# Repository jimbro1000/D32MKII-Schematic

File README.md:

# Dragon 32 MKII Schematic

Captured in KiCad by Stewart Orchard 2015-2019

Original design by Dragon Data Ltd circa 1982

PCB Reproduction by Julian Brown 2023

## Why?

The published Dragon schematics do not appear to include MKII versions, which can be a problem for repairs as there are differences in the memory configuration, the video circuit and logic gate pin numbers. I captured this information around the year 1998 with reference to the existing ISS2 schematics, a multimeter and a real MKII ISS6 main board, and have finally got round to recording it as a KiCad project.

## Disclaimer

Much as I would like to think that I've got this 100% correct, there is always the chance that there are mistakes and omissions. I would recommend checking that the information is accurate before using this schematic for anything potentially expensive.

## PCB Design

The PCB layout has been added to further assist with rapid identification of components and 
interconnections between components

This is not an attempt to reverse-engineer the board for production and no support will be given

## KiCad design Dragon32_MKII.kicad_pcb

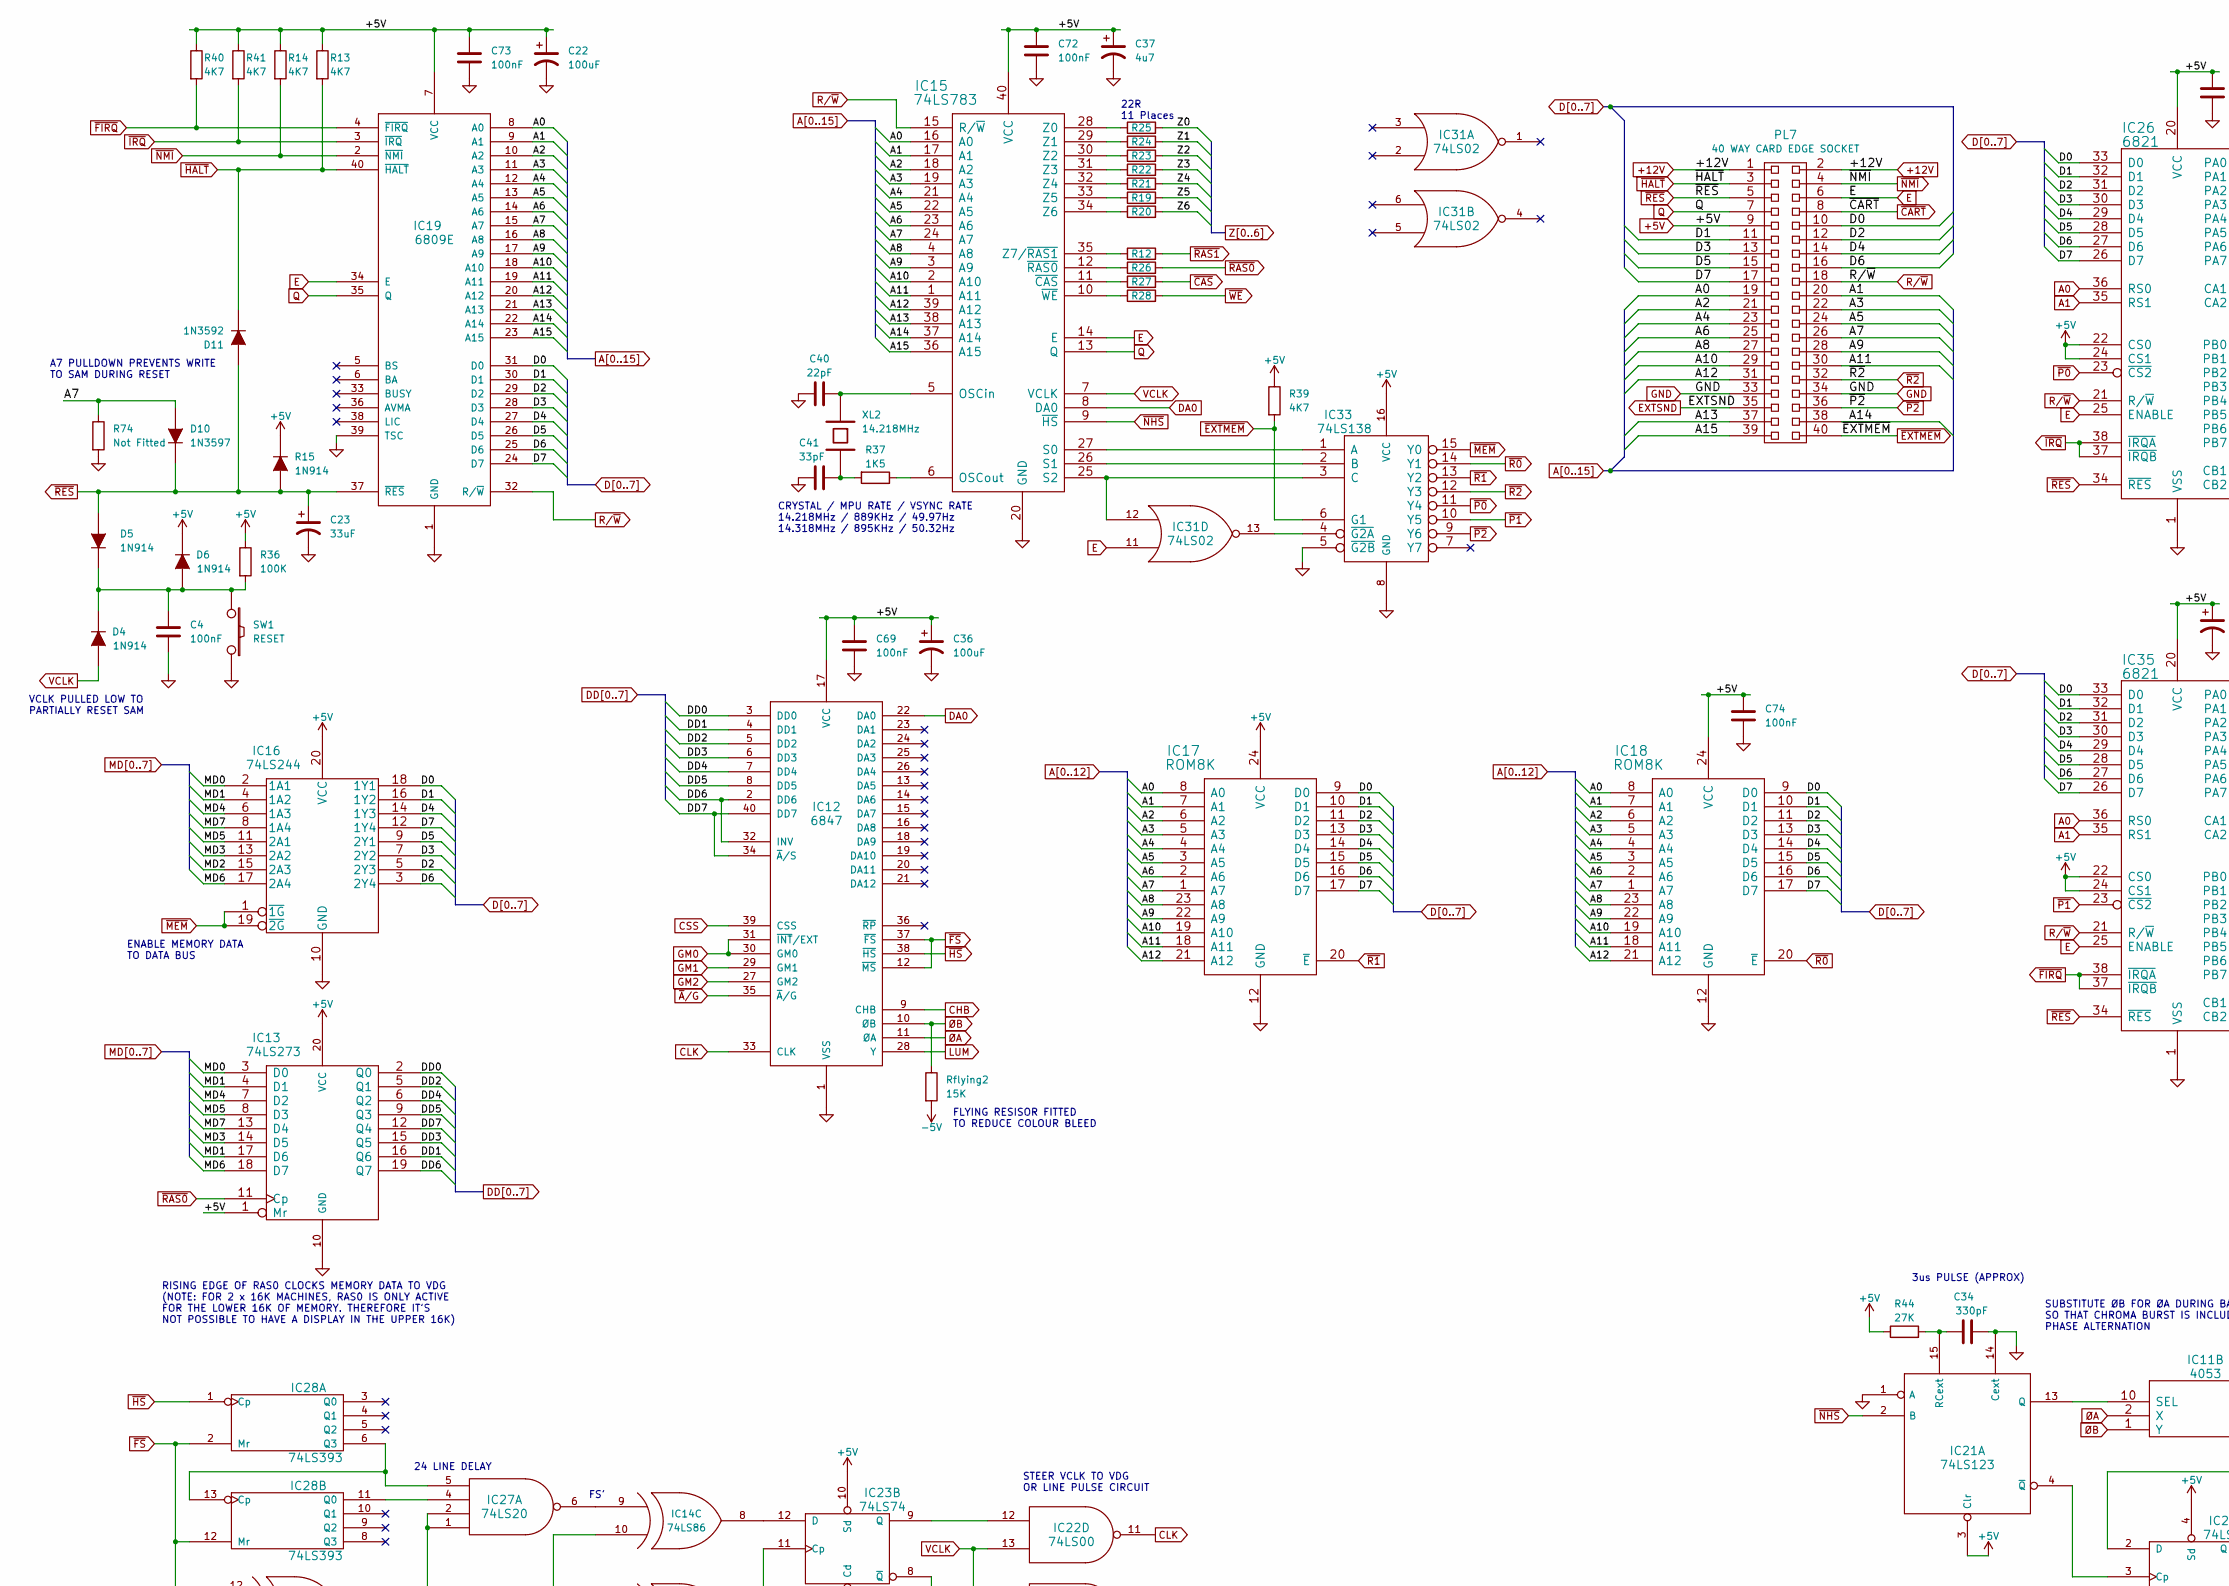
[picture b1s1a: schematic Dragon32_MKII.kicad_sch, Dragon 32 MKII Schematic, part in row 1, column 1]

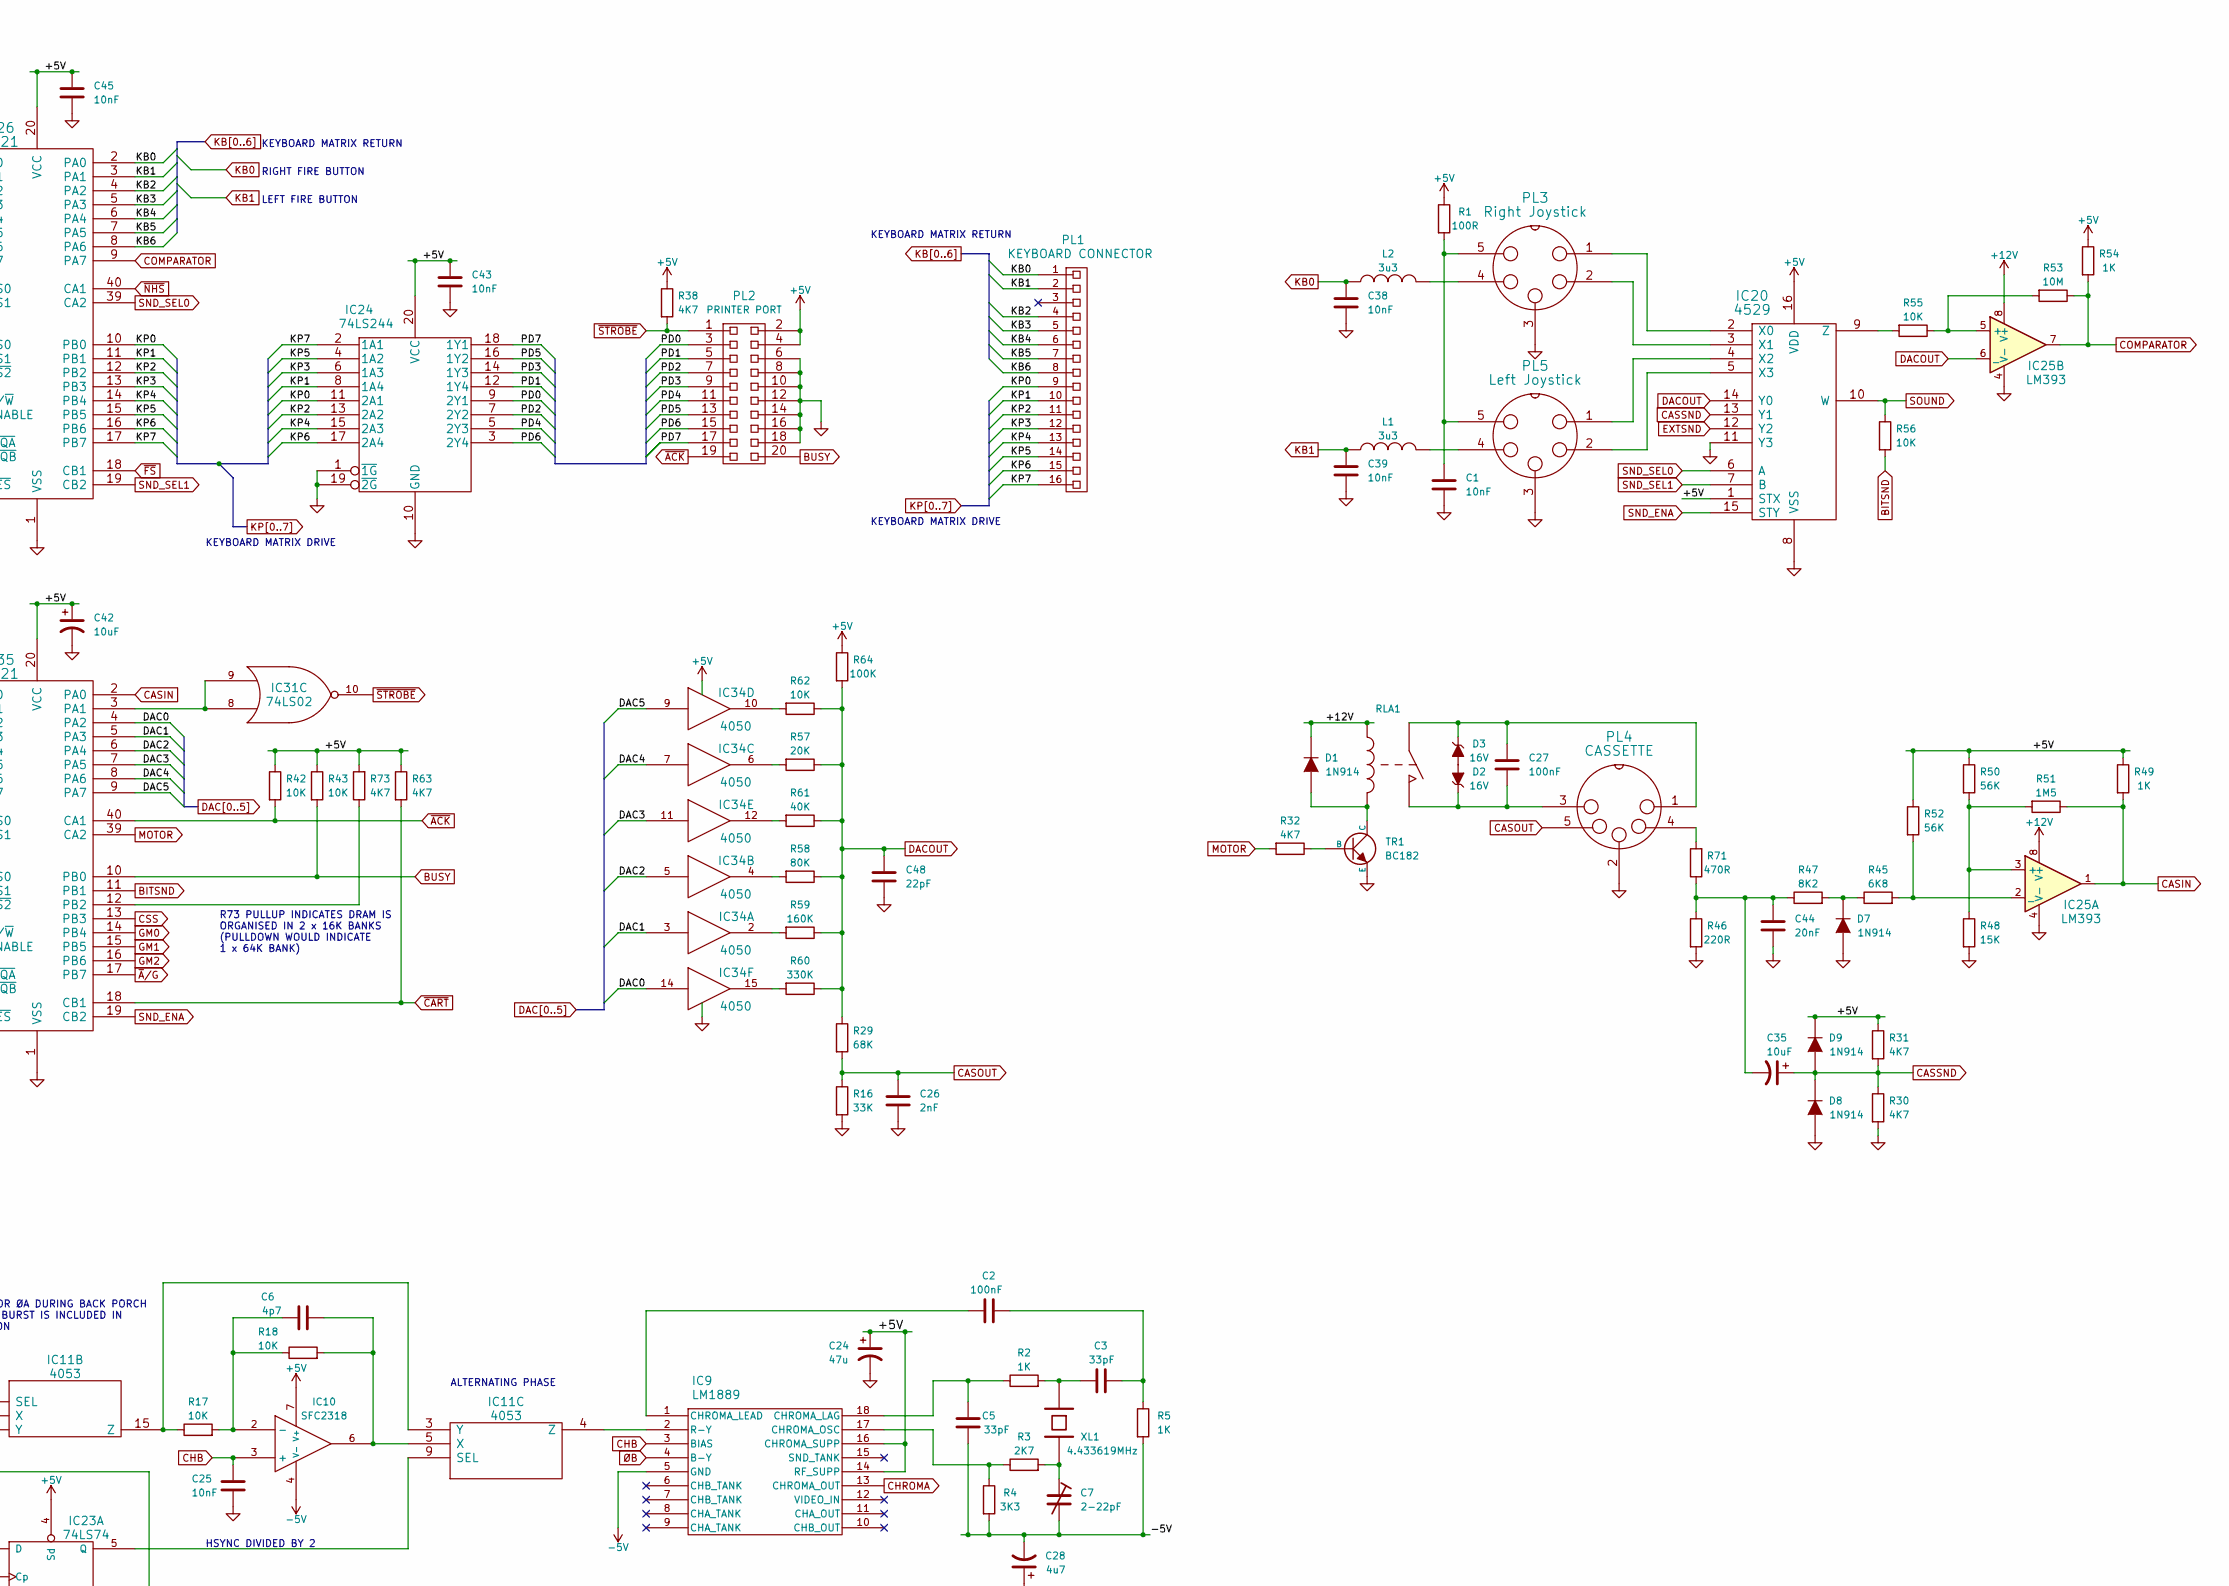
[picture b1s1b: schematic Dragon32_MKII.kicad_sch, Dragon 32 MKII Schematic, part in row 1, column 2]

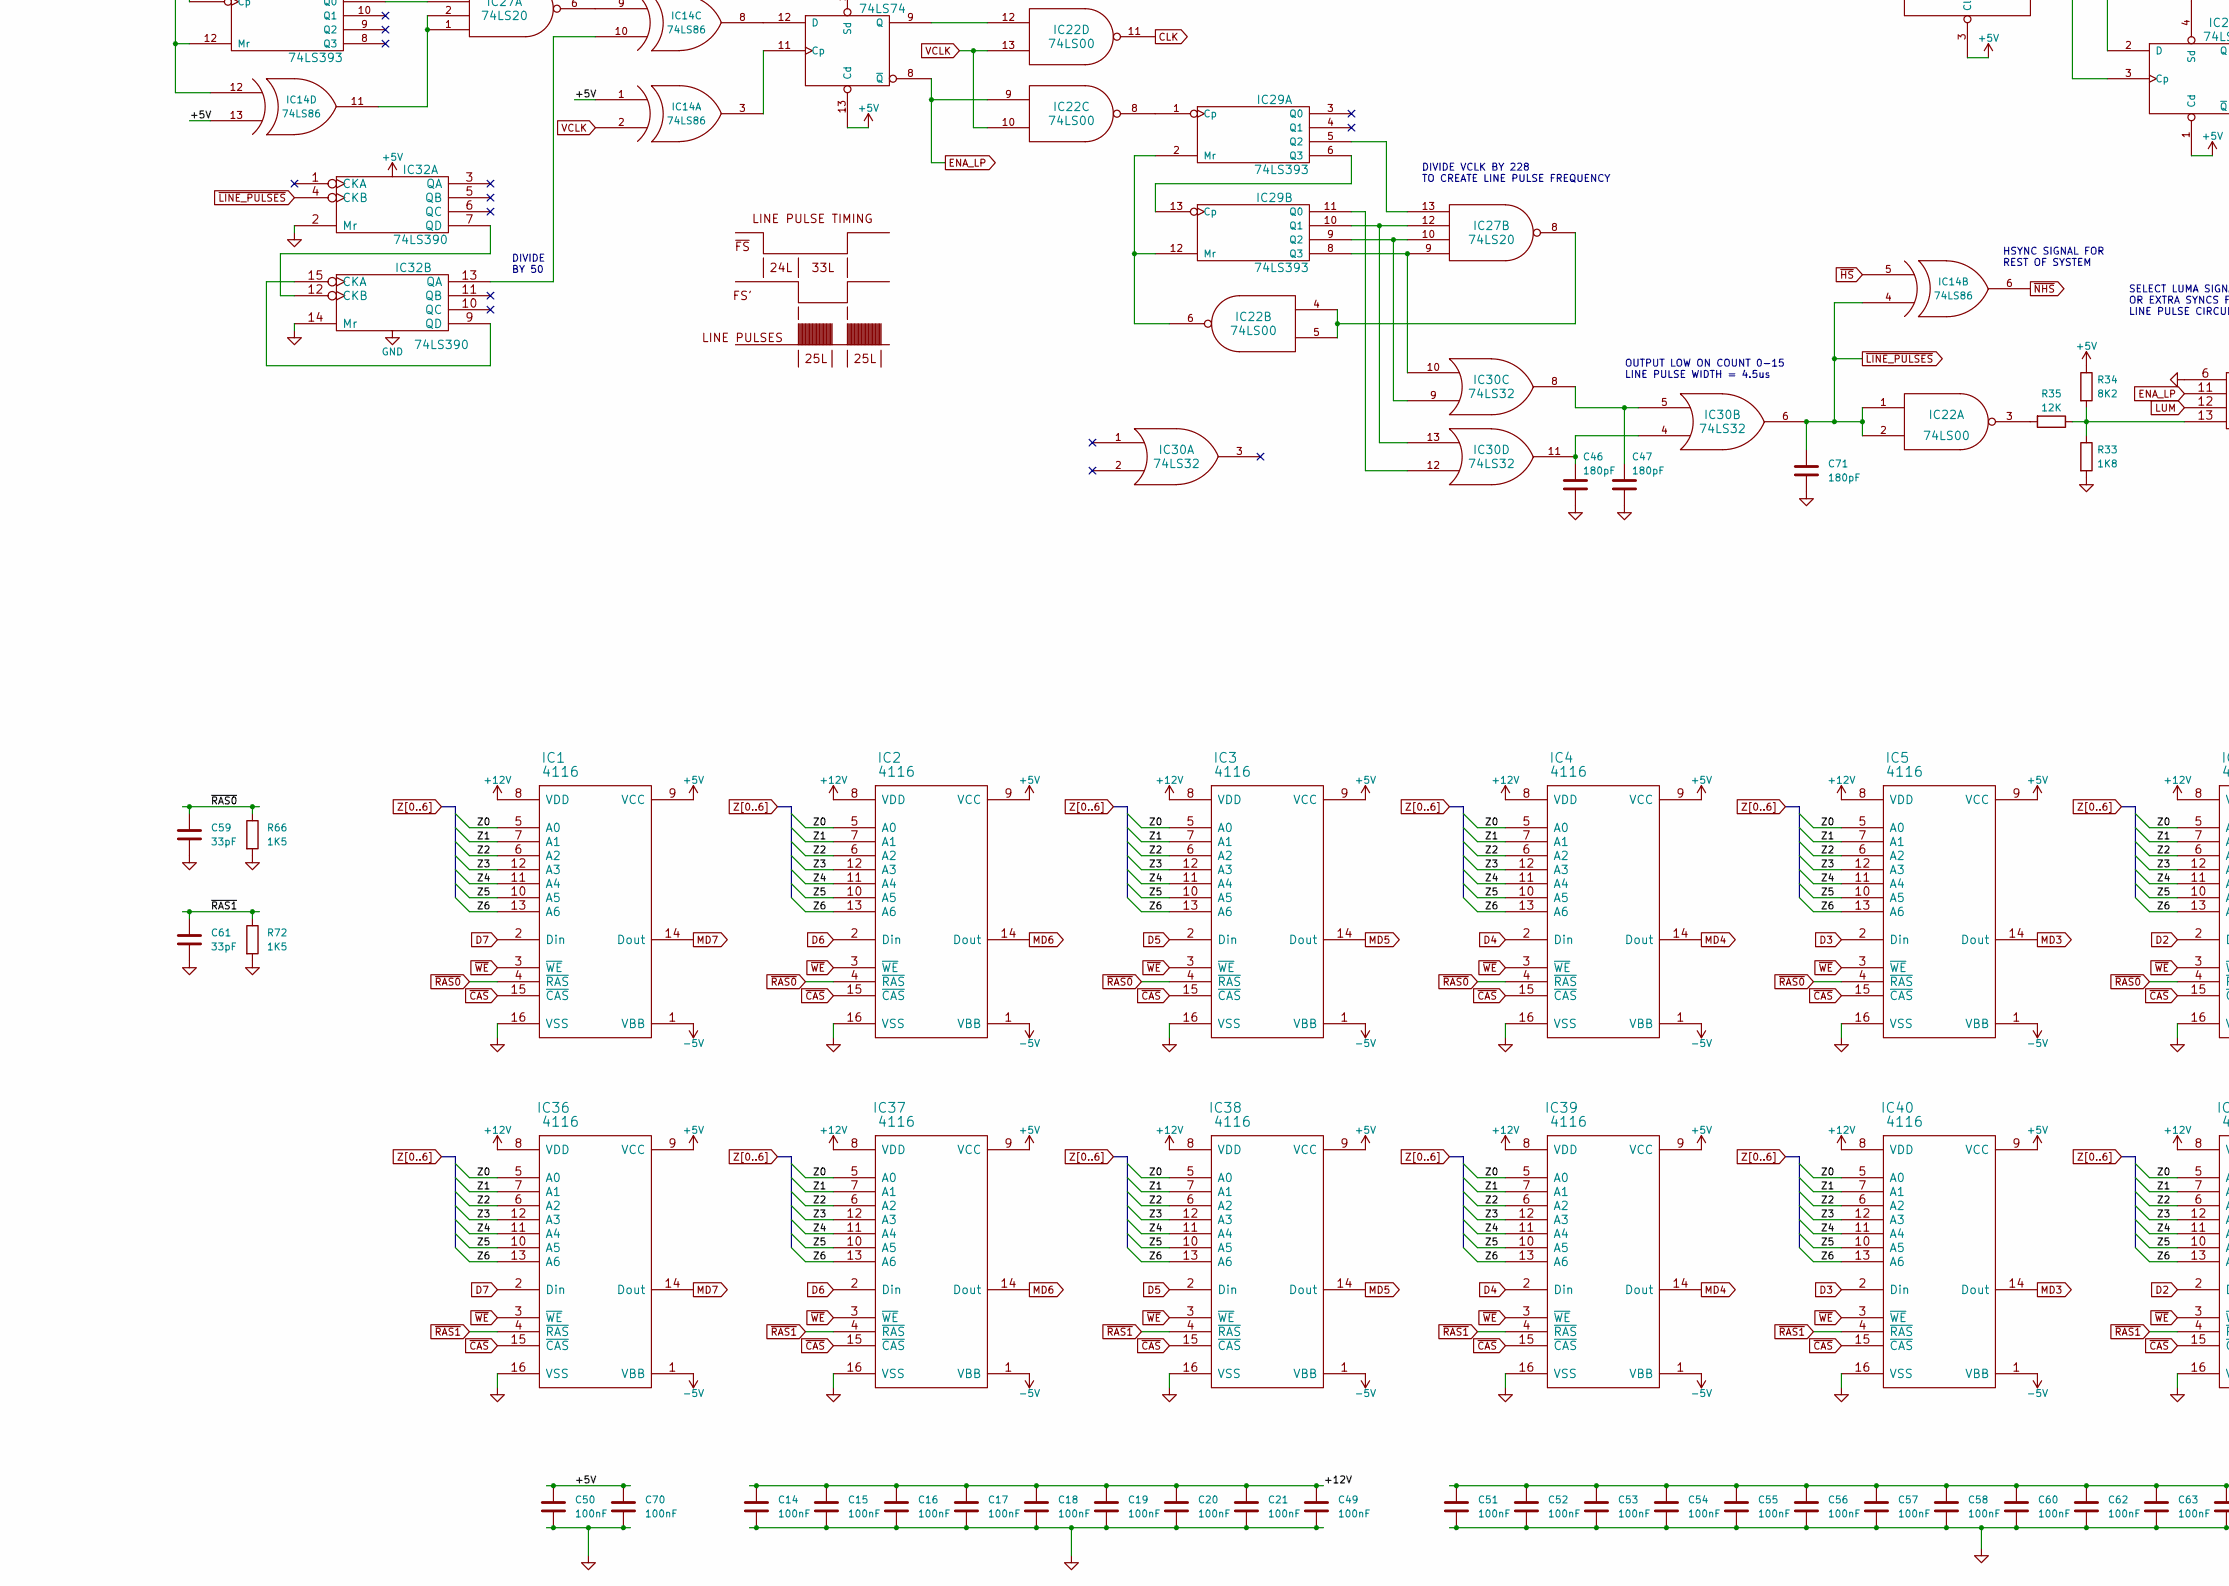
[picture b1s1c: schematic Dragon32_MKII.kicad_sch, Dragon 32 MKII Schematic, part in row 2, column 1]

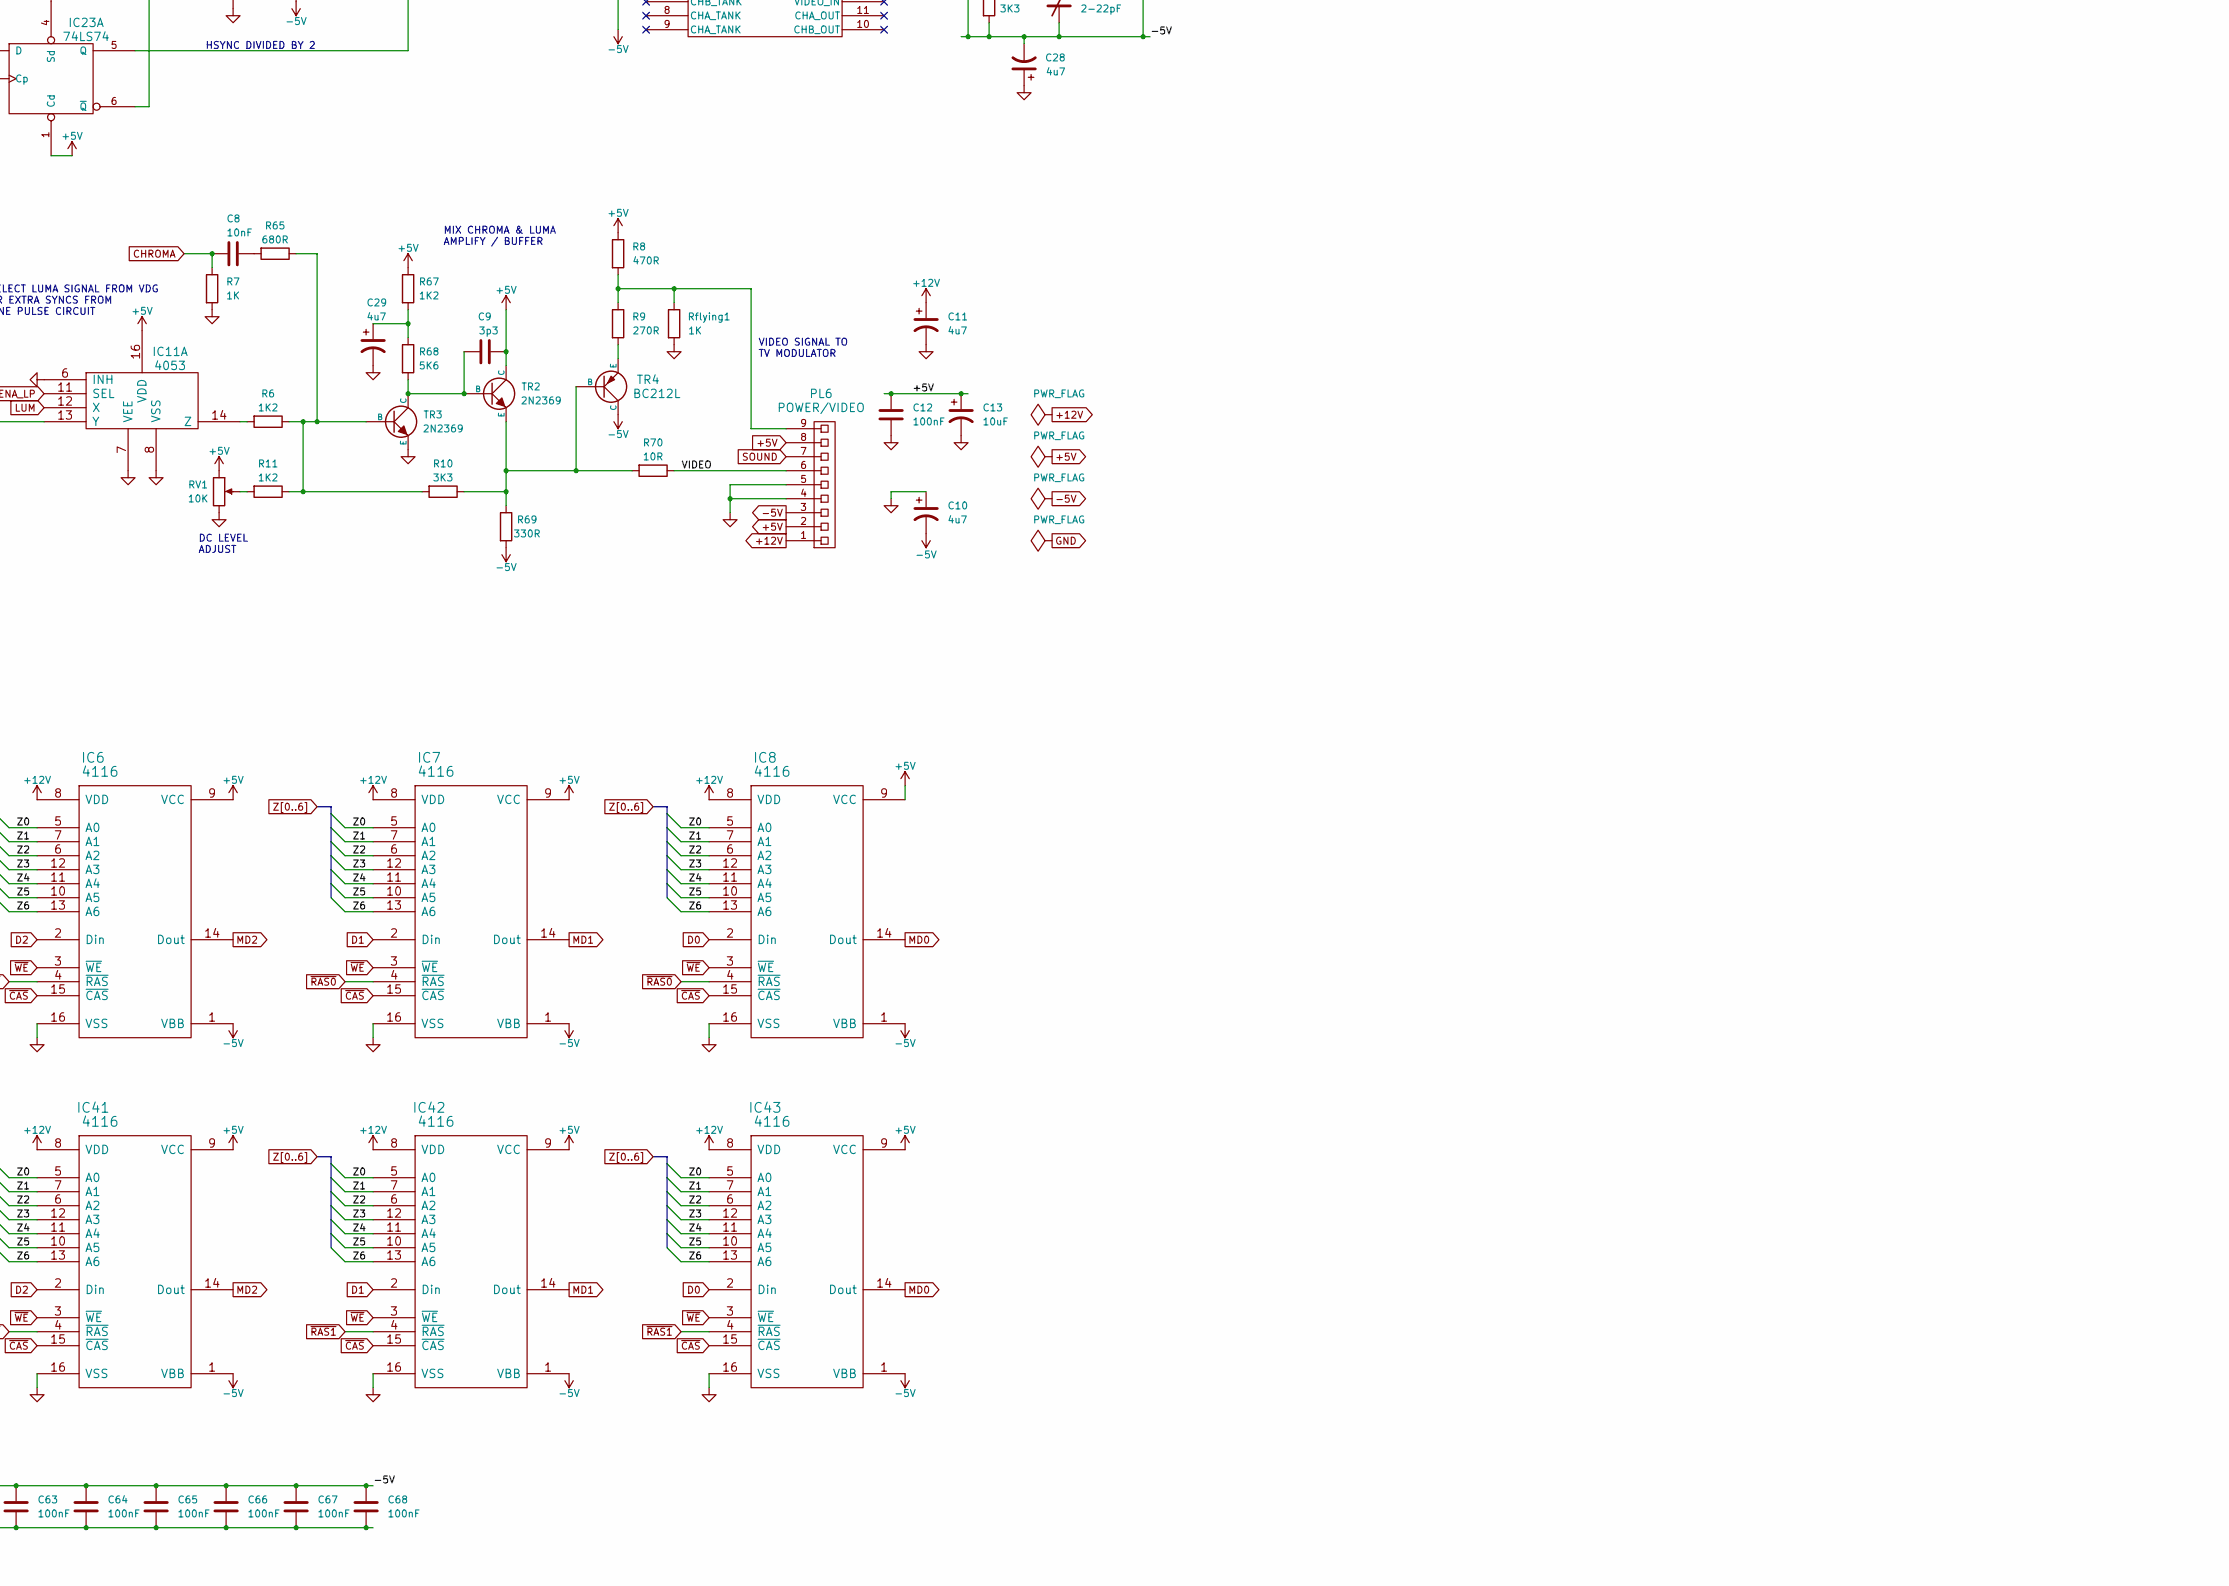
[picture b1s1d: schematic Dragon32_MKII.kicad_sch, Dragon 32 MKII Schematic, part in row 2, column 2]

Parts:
C1, C8, C25, C38, C39, C43, C45: 10nF; C_Disc_D4.3mm_W1.9mm_P5.00mm
C2, C4, C12, C14, C15, C16, C17, C18, C19, C20, C21, C27, C49, C50, C51, C52, C53, C54, C55, C56, C57, C58, C60, C62, C63, C64, C65, C66, C67, C68, C69, C70, C72, C73, C74: 100nF; C_Disc_D4.3mm_W1.9mm_P5.00mm
C3, C5, C41, C59, C61: 33pF; C_Disc_D3.0mm_W2.0mm_P2.50mm
C6: 4p7; C_Disc_D3.0mm_W2.0mm_P2.50mm
C7: 2-22pF; Trimmer-7.5mm
C9: 3p3; C_Disc_D3.0mm_W2.0mm_P2.50mm
C10, C11, C28, C29, C37: 4u7; CP_Radial_D5.0mm_P2.50mm
C13, C35, C42: 10uF; CP_Radial_D5.0mm_P2.50mm
C22, C36: 100uF; CP_Radial_D6.3mm_P2.50mm
C23: 33uF; CP_Radial_D5.0mm_P2.50mm
C24: 47u; CP_Radial_D5.0mm_P2.50mm
C26: 2nF; C_Disc_D3.0mm_W2.0mm_P2.50mm
C34: 330pF; C_Disc_D3.0mm_W2.0mm_P2.50mm
C40, C48: 22pF; C_Disc_D3.0mm_W2.0mm_P2.50mm
C44: 20nF; C_Disc_D5.0mm_W2.5mm_P5.00mm
C46, C47: 180pF; C_Disc_D3.0mm_W2.0mm_P2.50mm
C71: 180pF; C_Disc_D3.8mm_W2.6mm_P2.50mm
D1, D4, D5, D6, D7, D8, D9: 1N914; D_DO-35_SOD27_P7.62mm_Horizontal
D2, D3: 16V; D_DO-35_SOD27_P7.62mm_Horizontal
D10: 1N3597; D_DO-35_SOD27_P7.62mm_Horizontal
D11: 1N3592; D_DO-35_SOD27_P12.70mm_Horizontal
IC1, IC2, IC3, IC4, IC5, IC6, IC7, IC8, IC36, IC37, IC38, IC39, IC40, IC41, IC42, IC43: 4116; DIP-16_W7.62mm
IC9: LM1889; DIP-18_W7.62mm
IC10: SFC2318; DIP-8_W7.62mm
IC11: 4053; DIP-16_W7.62mm
IC12: 6847; DIP-40_W15.24mm
IC13: 74LS273; DIP-20_W7.62mm
IC14: 74LS86; DIP-14_W7.62mm
IC15: 74LS783; DIP-40_W15.24mm
IC16, IC24: 74LS244; DIP-20_W7.62mm
IC17, IC18: ROM8K; DIP-24_W15.24mm
IC19: 6809E; DIP-40_W15.24mm
IC20: 4529; DIP-16_W7.62mm
IC21: 74LS123; DIP-16_W7.62mm
IC22: 74LS00; DIP-14_W7.62mm
IC23: 74LS74; DIP-14_W7.62mm
IC25: LM393; DIP-8_W7.62mm
IC26, IC35: 6821; DIP-40_W15.24mm
IC27: 74LS20; DIP-14_W7.62mm
IC28, IC29: 74LS393; DIP-14_W7.62mm
IC30: 74LS32; DIP-14_W7.62mm
IC31: 74LS02; DIP-14_W7.62mm
IC32: 74LS390; DIP-16_W7.62mm
IC33: 74LS138; DIP-16_W7.62mm
IC34: 4050; DIP-16_W7.62mm
L1, L2: 3u3; L_Axial_L7.0mm_D3.3mm_P10.16mm_Horizontal_Fastron_MICC
PL1: KEYBOARD CONNECTOR; PinHeader_1x16_P2.54mm_Vertical
PL2: PRINTER PORT; IDC-Header_2x10-1MP_P2.54mm_Latch_Horizontal
PL3: Right Joystick; DIN-5_DELTRON_671-0501_45deg_Horizontal
PL4: CASSETTE; DIN-5_DELTRON_671-0501_45deg_Horizontal
PL5: Left Joystick; DIN-5_DELTRON_671-0501_45deg_Horizontal
PL6: POWER/VIDEO; Molex_KK-396_A-41791-0009_1x09_P3.96mm_Vertical
PL7: 40 WAY CARD EDGE SOCKET; Edge_2x20_P2.54mm_OvalMP
R1: 100R; R_Axial_DIN0207_L6.3mm_D2.5mm_P12.7mm_Horizontal
R2, R5, R7, R49, R54: 1K; R_Axial_DIN0207_L6.3mm_D2.5mm_P12.7mm_Horizontal
R3: 2K7; R_Axial_DIN0207_L6.3mm_D2.5mm_P12.7mm_Horizontal
R4: 3K3; R_Axial_DIN0207_L6.3mm_D2.5mm_P12.7mm_Horizontal
R6, R11: 1K2; R_Axial_DIN0207_L6.3mm_D2.5mm_P12.7mm_Horizontal
R8: 470R; R_Axial_DIN0207_L6.3mm_D2.5mm_P10.16mm_Horizontal
R9: 270R; R_Axial_DIN0207_L6.3mm_D2.5mm_P10.16mm_Horizontal
R10: 3K3; R_Axial_DIN0207_L6.3mm_D2.5mm_P10.16mm_Horizontal
R12, R19, R20, R21, R22, R23, R24, R25, R26, R27, R28: 22R; R_Axial_DIN0207_L6.3mm_D2.5mm_P12.7mm_Horizontal
R13, R14, R30, R31, R32, R38, R39, R40, R41, R63, R73: 4K7; R_Axial_DIN0207_L6.3mm_D2.5mm_P12.7mm_Horizontal
R15: 1N914; R_Axial_DIN0207_L6.3mm_D2.5mm_P12.7mm_Horizontal
R16: 33K; R_Axial_DIN0207_L6.3mm_D2.5mm_P12.7mm_Horizontal
R17, R18, R42, R43, R55, R56, R62: 10K; R_Axial_DIN0207_L6.3mm_D2.5mm_P12.7mm_Horizontal
R29: 68K; R_Axial_DIN0207_L6.3mm_D2.5mm_P12.7mm_Horizontal
R33: 1K8; R_Axial_DIN0207_L6.3mm_D2.5mm_P12.7mm_Horizontal
R34, R47: 8K2; R_Axial_DIN0207_L6.3mm_D2.5mm_P12.7mm_Horizontal
R35: 12K; R_Axial_DIN0207_L6.3mm_D2.5mm_P12.7mm_Horizontal
R36, R64: 100K; R_Axial_DIN0207_L6.3mm_D2.5mm_P12.7mm_Horizontal
R37, R66, R72: 1K5; R_Axial_DIN0207_L6.3mm_D2.5mm_P12.7mm_Horizontal
R44: 27K; R_Axial_DIN0207_L6.3mm_D2.5mm_P12.7mm_Horizontal
R45: 6K8; R_Axial_DIN0207_L6.3mm_D2.5mm_P12.7mm_Horizontal
R46: 220R; R_Axial_DIN0207_L6.3mm_D2.5mm_P12.7mm_Horizontal
R48: 15K; R_Axial_DIN0207_L6.3mm_D2.5mm_P12.7mm_Horizontal
R50, R52: 56K; R_Axial_DIN0207_L6.3mm_D2.5mm_P12.7mm_Horizontal
R51: 1M5; R_Axial_DIN0207_L6.3mm_D2.5mm_P12.7mm_Horizontal
R53: 10M; R_Axial_DIN0207_L6.3mm_D2.5mm_P12.7mm_Horizontal
R57: 20K; R_Axial_DIN0207_L6.3mm_D2.5mm_P12.7mm_Horizontal
R58: 80K; R_Axial_DIN0207_L6.3mm_D2.5mm_P12.7mm_Horizontal
R59: 160K; R_Axial_DIN0207_L6.3mm_D2.5mm_P12.7mm_Horizontal
R60: 330K; R_Axial_DIN0207_L6.3mm_D2.5mm_P12.7mm_Horizontal
R61: 40K; R_Axial_DIN0207_L6.3mm_D2.5mm_P12.7mm_Horizontal
R65: 680R; R_Axial_DIN0207_L6.3mm_D2.5mm_P12.7mm_Horizontal
R67: 1K2; R_Axial_DIN0207_L6.3mm_D2.5mm_P10.16mm_Horizontal
R68: 5K6; R_Axial_DIN0207_L6.3mm_D2.5mm_P10.16mm_Horizontal
R69: 330R; R_Axial_DIN0207_L6.3mm_D2.5mm_P10.16mm_Horizontal
R70: 10R; R_Axial_DIN0207_L6.3mm_D2.5mm_P10.16mm_Horizontal
R71: 470R; R_Axial_DIN0207_L6.3mm_D2.5mm_P12.7mm_Horizontal
R74: Not Fitted
RLA1: RELAY; OJS HM 10A Relay
RV1: 10K; Potentiometer_Bourns_3386X_Horizontal
Rflying1: 1K
Rflying2: 15K
SW1: RESET; Button_AlpsAlpine_SPUN190900
TR1: BC182; TO-92L_Inline_Wide
TR2, TR3: 2N2369; TO-92L_Inline_Wide
TR4: BC212L; TO-92L_Inline_Wide
U1: LINE_PULSE_DIAGRAM
XL1: 4.433619MHz; Crystal_HC49-U_Horizontal
XL2: 14.218MHz; Crystal_HC49-U_Horizontal

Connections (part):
+5V: C9.2, C12.1, C13.1, C22.1, C24.1, C36.1, C37.1, C42.1, C43.1, C45.1, C50.1, C69.1, C70.1, C72.1, C73.1, C74.1, D6.2 (K), D9.2 (K), IC1.9 (VCC), IC2.9 (VCC), IC3.9 (VCC), IC4.9 (VCC), IC5.9 (VCC), IC6.9 (VCC), IC7.9 (VCC), IC8.9 (VCC), IC9.14 (RF_SUPP), IC9.16 (CHROMA_SUPP), IC10.7 (V+), IC11.16 (VDD), IC12.17 (VCC), IC13.1 (Mr), IC13.20 (VCC), IC14.1 (IN1), IC14.13 (IN2), IC14.14 (VCC), IC15.40 (VCC), IC16.20 (VCC), IC17.24 (VCC), IC18.24 (VCC), IC19.7 (VCC), IC20.1 (STX), IC20.16 (VDD), IC21.3 (Clr), IC21.16 (VCC), IC22.14 (VCC), IC23.1 (Cd), IC23.4 (Sd), IC23.10 (Sd), IC23.13 (Cd), IC23.14 (VCC), IC24.20 (VCC), IC26.20 (VCC), IC26.22 (CS0), IC26.24 (CS1), IC27.14 (VCC), IC28.14 (VCC), IC29.14 (VCC), IC30.14 (VCC), IC31.14 (VCC), IC32.16 (VCC), IC33.16 (VCC), IC34.1 (VCC), IC35.20 (VCC), IC35.22 (CS0), IC35.24 (CS1), IC36.9 (VCC), IC37.9 (VCC), IC38.9 (VCC), IC39.9 (VCC), IC40.9 (VCC), IC41.9 (VCC), IC42.9 (VCC), IC43.9 (VCC), PL2.2, PL2.4, PL6.2, PL6.8, PL7.9, R1.1, R8.1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
+12V: C11.1, C14.1, C15.1, C16.1, C17.1, C18.1, C19.1, C20.1, C21.1, C49.1, D1.2 (K), IC1.8 (VDD), IC2.8 (VDD), IC3.8 (VDD), IC4.8 (VDD), IC5.8 (VDD), IC6.8 (VDD), IC7.8 (VDD), IC8.8 (VDD), IC25.8 (V+), IC36.8 (VDD), IC37.8 (VDD), IC38.8 (VDD), IC39.8 (VDD), IC40.8 (VDD), IC41.8 (VDD), IC42.8 (VDD), IC43.8 (VDD), PL6.1, PL7.1, PL7.2, RLA1.1
-5V: C5.1, C7.2, C10.2, C28.2, C51.1, C52.1, C53.1, C54.1, C55.1, C56.1, C57.1, C58.1, C60.1, C62.1, C63.1, C64.1, C65.1, C66.1, C67.1, C68.1, IC1.1 (VBB), IC2.1 (VBB), IC3.1 (VBB), IC4.1 (VBB), IC5.1 (VBB), IC6.1 (VBB), IC7.1 (VBB), IC8.1 (VBB), IC9.5 (GND), IC10.4 (V-), IC36.1 (VBB), IC37.1 (VBB), IC38.1 (VBB), IC39.1 (VBB), IC40.1 (VBB), IC41.1 (VBB), IC42.1 (VBB), IC43.1 (VBB), PL6.3, R4.2, R5.2, R69.2, Rflying2.2, TR4.3 (C)
/PD0: IC24.9 (2Y1), PL2.3
/PD1: IC24.12 (1Y4), PL2.5
/PD2: IC24.7 (2Y2), PL2.7
/PD3: IC24.14 (1Y3), PL2.9
/PD4: IC24.5 (2Y3), PL2.11
/PD5: IC24.16 (1Y2), PL2.13
/PD6: IC24.3 (2Y4), PL2.15
/PD7: IC24.18 (1Y1), PL2.17
/VIDEO: PL6.6, R70.1
A0: IC15.16 (A0), IC17.8 (A0), IC18.8 (A0), IC19.8 (A0), IC26.36 (RS0), IC35.36 (RS0), PL7.19
A1: IC15.17 (A1), IC17.7 (A1), IC18.7 (A1), IC19.9 (A1), IC26.35 (RS1), IC35.35 (RS1), PL7.20
A2: IC15.18 (A2), IC17.6 (A2), IC18.6 (A2), IC19.10 (A2), PL7.21
A3: IC15.19 (A3), IC17.5 (A3), IC18.5 (A3), IC19.11 (A3), PL7.22
A4: IC15.21 (A4), IC17.4 (A4), IC18.4 (A4), IC19.12 (A4), PL7.23
A5: IC15.22 (A5), IC17.3 (A5), IC18.3 (A5), IC19.13 (A5), PL7.24
A6: IC15.23 (A6), IC17.2 (A6), IC18.2 (A6), IC19.14 (A6), PL7.25
A7: D10.1 (A), IC15.24 (A7), IC17.1 (A7), IC18.1 (A7), IC19.15 (A7), PL7.26, R74.1
A8: IC15.4 (A8), IC17.23 (A8), IC18.23 (A8), IC19.16 (A8), PL7.27
A9: IC15.3 (A9), IC17.22 (A9), IC18.22 (A9), IC19.17 (A9), PL7.28
A10: IC15.2 (A10), IC17.19 (A10), IC18.19 (A10), IC19.18 (A10), PL7.29
A11: IC15.1 (A11), IC17.18 (A11), IC18.18 (A11), IC19.19 (A11), PL7.30
A12: IC15.39 (A12), IC17.21 (A12), IC18.21 (A12), IC19.20 (A12), PL7.31
A13: IC15.38 (A13), IC19.21 (A13), PL7.37
A14: IC15.37 (A14), IC19.22 (A14), PL7.38
A15: IC15.36 (A15), IC19.23 (A15), PL7.39
BITSND: IC35.11 (PB1), R56.2
BUSY: IC35.10 (PB0), PL2.20, R43.2
CASIN: IC25.1, IC35.2 (PA0), R49.2, R51.1
CASOUT: C26.1, PL4.5, R16.1, R29.2
CASSND: C35.1, D8.2 (K), D9.1 (A), IC20.13 (Y1), R30.1, R31.2
CHB: C25.1, IC9.3 (BIAS), IC10.3 (+), IC12.9 (CHB)
CHROMA: C8.2, IC9.13 (CHROMA_OUT), R7.1
CLK: IC12.33 (CLK), IC22.11
COMPARATOR: IC25.7, IC26.9 (PA7), R53.1, R54.2
CSS: IC12.39 (CSS), IC35.13 (PB3)
D0: IC8.2 (Din), IC16.18 (1Y1), IC17.9 (D0), IC18.9 (D0), IC19.31 (D0), IC26.33 (D0), IC35.33 (D0), IC43.2 (Din), PL7.10
D1: IC7.2 (Din), IC16.16 (1Y2), IC17.10 (D1), IC18.10 (D1), IC19.30 (D1), IC26.32 (D1), IC35.32 (D1), IC42.2 (Din), PL7.11
D2: IC6.2 (Din), IC16.5 (2Y3), IC17.11 (D2), IC18.11 (D2), IC19.29 (D2), IC26.31 (D2), IC35.31 (D2), IC41.2 (Din), PL7.12
D3: IC5.2 (Din), IC16.7 (2Y2), IC17.13 (D3), IC18.13 (D3), IC19.28 (D3), IC26.30 (D3), IC35.30 (D3), IC40.2 (Din), PL7.13
D4: IC4.2 (Din), IC16.14 (1Y3), IC17.14 (D4), IC18.14 (D4), IC19.27 (D4), IC26.29 (D4), IC35.29 (D4), IC39.2 (Din), PL7.14
D5: IC3.2 (Din), IC16.9 (2Y1), IC17.15 (D5), IC18.15 (D5), IC19.26 (D5), IC26.28 (D5), IC35.28 (D5), IC38.2 (Din), PL7.15
D6: IC2.2 (Din), IC16.3 (2Y4), IC17.16 (D6), IC18.16 (D6), IC19.25 (D6), IC26.27 (D6), IC35.27 (D6), IC37.2 (Din), PL7.16
D7: IC1.2 (Din), IC16.12 (1Y4), IC17.17 (D7), IC18.17 (D7), IC19.24 (D7), IC26.26 (D7), IC35.26 (D7), IC36.2 (Din), PL7.17
DA0: IC12.22 (DA0), IC15.8 (DA0)
DAC0: IC34.14, IC35.4 (PA2)
DAC1: IC34.3, IC35.5 (PA3)
DAC2: IC34.5, IC35.6 (PA4)
DAC3: IC34.11, IC35.7 (PA5)
DAC4: IC34.7, IC35.8 (PA6)
DAC5: IC34.9, IC35.9 (PA7)
DACOUT: C48.1, IC20.14 (Y0), IC25.6 (_), R29.1, R57.1, R58.1, R59.1, R60.1, R61.1, R62.1, R64.2
DD0: IC12.3 (DD0), IC13.2 (Q0)
DD1: IC12.4 (DD1), IC13.16 (Q6)
DD2: IC12.5 (DD2), IC13.5 (Q1)
DD3: IC12.6 (DD3), IC13.15 (Q5)
DD4: IC12.7 (DD4), IC13.6 (Q2)
DD5: IC12.8 (DD5), IC13.9 (Q3)
DD6: IC12.2 (DD6), IC12.32 (INV), IC13.19 (Q7)
DD7: IC12.34 (~A/S), IC12.40 (DD7), IC13.12 (Q4)
E: IC15.14 (E), IC19.34 (E), IC26.25 (ENABLE), IC31.11, IC35.25 (ENABLE), PL7.6
ENA_LP: IC11.11 (SEL), IC22.9, IC23.8 (~Q)
EXTSND: IC20.12 (Y2), PL7.35
GM0: IC12.30 (GM0), IC12.31 (~INT/EXT), IC35.14 (PB4)
GM1: IC12.29 (GM1), IC35.15 (PB5)
GM2: IC12.27 (GM2), IC35.16 (PB6)
GND: C1.2, C4.2, C10.1, C11.2, C12.2, C13.2, C14.2, C15.2, C16.2, C17.2, C18.2, C19.2, C20.2, C21.2, C22.2, C23.2, C24.2, C25.2, C26.2, C28.1, C29.2, C34.2, C36.2, C37.2, C38.2, C39.2, C40.2, C41.2, C42.2, C43.2, C44.2, C45.2, C46.2, C47.2, C48.2, C49.2, C50.2, C51.2, C52.2, C53.2, C54.2, C55.2, C56.2, C57.2, C58.2, C59.2, C60.2, C61.2, C62.2, C63.2, C64.2, C65.2, C66.2, C67.2, C68.2, C69.2, C70.2, C71.2, C72.2, C73.2, C74.2, D7.1 (A), D8.1 (A), IC1.16 (VSS), IC2.16 (VSS), IC3.16 (VSS), IC4.16 (VSS), IC5.16 (VSS), IC6.16 (VSS), IC7.16 (VSS), IC8.16 (VSS), IC11.6 (INH), IC11.7 (VEE), IC11.8 (VSS), IC12.1 (VSS), IC13.10 (GND), IC14.7 (GND), IC15.20 (GND), IC16.10 (GND), IC17.12 (GND), IC18.12 (GND)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
KB0: C38.1, IC26.2 (PA0), L2.1, PL1.1
KB1: C39.1, IC26.3 (PA1), L1.1, PL1.2
KB2: IC26.4 (PA2), PL1.4
KB3: IC26.5 (PA3), PL1.5
KB4: IC26.6 (PA4), PL1.6
KB5: IC26.7 (PA5), PL1.7
KB6: IC26.8 (PA6), PL1.8
KP0: IC24.11 (2A1), IC26.10 (PB0), PL1.9
KP1: IC24.8 (1A4), IC26.11 (PB1), PL1.10
KP2: IC24.13 (2A2), IC26.12 (PB2), PL1.11
KP3: IC24.6 (1A3), IC26.13 (PB3), PL1.12
KP4: IC24.15 (2A3), IC26.14 (PB4), PL1.13
KP5: IC24.4 (1A2), IC26.15 (PB5), PL1.14
KP6: IC24.17 (2A4), IC26.16 (PB6), PL1.15
KP7: IC24.2 (1A1), IC26.17 (PB7), PL1.16
LUM: IC11.12 (X), IC12.28 (Y)
MD0: IC8.14 (Dout), IC13.3 (D0), IC16.2 (1A1), IC43.14 (Dout)
MD1: IC7.14 (Dout), IC13.4 (D1), IC13.17 (D6), IC16.4 (1A2), IC42.14 (Dout)
MD2: IC6.14 (Dout), IC16.15 (2A3), IC41.14 (Dout)
MD3: IC5.14 (Dout), IC13.14 (D5), IC16.13 (2A2), IC40.14 (Dout)
MD4: IC4.14 (Dout), IC13.7 (D2), IC16.6 (1A3), IC39.14 (Dout)
MD5: IC3.14 (Dout), IC13.8 (D3), IC16.11 (2A1), IC38.14 (Dout)
MD6: IC2.14 (Dout), IC13.18 (D7), IC16.17 (2A4), IC37.14 (Dout)
MD7: IC1.14 (Dout), IC13.13 (D4), IC16.8 (1A4), IC36.14 (Dout)
MOTOR: IC35.39 (CA2), R32.2
unnamed: C1.1, PL3.5, PL5.5, R1.2
unnamed: C2.2, C3.2, R5.1
unnamed: C3.1, R2.2, XL1.1
unnamed: C7.1, R3.2, XL1.2
unnamed: C8.1, R65.2
unnamed: C29.1, R67.2, R68.1
unnamed: C35.2, C44.1, R46.1, R47.1, R71.1
unnamed: C41.1, R37.2, XL2.2
unnamed: C46.1, IC30.4, IC30.11
unnamed: C47.1, IC30.5, IC30.8
unnamed: D1.1 (A), RLA1.2, TR1.1 (C)
unnamed: D2.1 (A), D3.1 (A)
unnamed: C27.2, D2.2 (K), PL4.3, RLA1.4
unnamed: C27.1, D3.2 (K), PL4.1, RLA1.3
unnamed: C4.1, D4.2 (K), D5.2 (K), D6.1 (A), R36.2, SW1.2
unnamed: D7.2 (K), R45.1, R47.2
unnamed: C5.2, IC9.18 (CHROMA_LAG), R2.1
unnamed: C2.1, IC9.1 (CHROMA_LEAD)
unnamed: IC9.17 (CHROMA_OSC), R3.1, R4.1
unnamed: C6.1, IC10.2 (-), R17.2, R18.1
unnamed: IC11.13 (Y), R33.1, R34.2, R35.1
unnamed: IC11.14 (Z), R6.2
unnamed: IC11.10 (SEL), IC21.13 (Q)
unnamed: IC11.3 (Y), IC11.15 (Z), R17.1
unnamed: IC11.9 (SEL), IC23.5 (Q)
unnamed: C6.2, IC10.6, IC11.5 (X), R18.2
unnamed: IC9.2 (R-Y), IC11.4 (Z)
unnamed: IC14.3 (OUT), IC23.11 (Cp)
unnamed: IC14.9 (IN1), IC27.6
unnamed: IC14.10 (IN2), IC32.13 (QA)
unnamed: IC14.8 (OUT), IC23.12 (D)
unnamed: IC14.11 (OUT), IC27.1, IC27.2
unnamed: C40.1, IC15.5 (OSCin), XL2.1
unnamed: IC15.6 (OSCout), R37.1
unnamed: IC15.27 (S0), IC33.1 (A)
unnamed: IC15.26 (S1), IC33.2 (B)
unnamed: IC15.25 (S2), IC31.12, IC33.3 (C)
unnamed: IC15.28 (Z0), R25.1
unnamed: IC15.29 (Z1), R24.1
unnamed: IC15.30 (Z2), R23.1
unnamed: IC15.31 (Z3), R22.1
unnamed: IC15.32 (Z4), R21.1
unnamed: IC15.33 (Z5), R19.1
unnamed: IC15.34 (Z6), R20.1
unnamed: IC15.35 (Z7/~RAS1), R12.1
unnamed: IC15.11 (~CAS), R27.1
unnamed: IC15.12 (~RAS0), R26.1
unnamed: IC15.10 (~WE), R28.1
unnamed: IC20.2 (X0), PL3.1
unnamed: IC20.3 (X1), PL3.2
unnamed: IC20.4 (X2), PL5.1
unnamed: IC20.5 (X3), PL5.2
unnamed: IC20.9 (Z), R55.2
unnamed: C34.1, IC21.15 (RCext), R44.2
unnamed: IC21.4 (~Q), IC23.3 (Cp)
unnamed: IC22.3, R35.2
unnamed: IC22.4, IC22.5, IC27.8
unnamed: IC23.2 (D), IC23.6 (~Q)
unnamed: IC22.12, IC23.9 (Q)
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
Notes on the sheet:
3us PULSE (APPROX)
DIVIDE VCLK BY 228 TO CREATE LINE PULSE FREQUENCY
DIVIDE BY 50
FLYING RESISOR FITTED TO REDUCE COLOUR BLEED
A7 PULLDOWN PREVENTS WRITE TO SAM DURING RESET
KEYBOARD MATRIX DRIVE
RISING EDGE OF RAS0 CLOCKS MEMORY DATA TO VDG (NOTE: FOR 2 x 16K MACHINES, RAS0 IS ONLY ACTIVE FOR THE LOWER 16K OF MEMORY. THEREFORE IT'S NOT POSSIBLE TO HAVE A DISPLAY IN THE UPPER 16K)
MIX CHROMA & LUMA AMPLIFY / BUFFER
RIGHT FIRE BUTTON
24 LINE DELAY
FS'
R73 PULLUP INDICATES DRAM IS ORGANISED IN 2 x 16K BANKS (PULLDOWN WOULD INDICATE 1 x 64K BANK)
KEYBOARD MATRIX RETURN
SUBSTITUTE ØB FOR ØA DURING BACK PORCH SO THAT CHROMA BURST IS INCLUDED IN PHASE ALTERNATION
22R 11 Places
CRYSTAL / MPU RATE / VSYNC RATE 14.218MHz / 889KHz / 49.97Hz 14.318MHz / 895KHz / 50.32Hz
HSYNC DIVIDED BY 2
STEER VCLK TO VDG OR LINE PULSE CIRCUIT
VCLK PULLED LOW TO PARTIALLY RESET SAM
ENABLE MEMORY DATA TO DATA BUS
DC LEVEL ADJUST
LEFT FIRE BUTTON
HSYNC SIGNAL FOR REST OF SYSTEM
ALTERNATING PHASE
OUTPUT LOW ON COUNT 0-15 LINE PULSE WIDTH = 4.5us
VIDEO SIGNAL TO TV MODULATOR
SELECT LUMA SIGNAL FROM VDG OR EXTRA SYNCS FROM LINE PULSE CIRCUIT

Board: 2 copper layers, 215 parts (0 on the bottom side), 228 nets, no tracks yet.

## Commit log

2023-07-10 add pcb to project
2023-07-10 align component positions to board
2023-07-10 add render
2023-07-12 more layout
2023-07-12 refresh render
2023-07-12 position components
2023-07-13 initial routing of ground plane
2023-07-15 reposition pcb components
2023-07-17 use scanned pcb images to locate components
2023-07-17 refine component locations
2023-07-17 trace routes
2023-07-18 more tracing
2023-07-18 yet more tracing
2023-07-18 complete tracing
2023-07-18 finish tracing with relay
2023-10-05 fix z1 z2 wiring
